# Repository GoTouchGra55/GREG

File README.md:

# GREG

GREG is a custom SBC designed to act as the main computer for a rover. It is built around the Allwinner T527 SoC and includes custom memory, power management, connectivity, camera, display, sensor, and motor-control hardware.

CAD REPO - [REPO](https://github.com/unknowngamer69/Orion-Rover)

## Hardware

- SoC: Allwinner T527
- RAM: 2 GB Samsung LPDDR4
- PMIC: AXP717-family
- Storage: MicroSD
- Networking: Ethernet
- Connectivity: 2× USB-A + 1× USB-C
- Display: HDMI + 5" LCD interface
- Cameras: 3-camera support (2 with multiplexing)
- Sensors: 6× ToF + LiDAR
- Debug: UART/debug connector
- Expansion: External breakout connector

## Motor Driver

Motor control is handled by a separate PCB instead of the T527.

- MCU: STM32G4
- Motor drivers: 3× DRV8262
- Motors: 6× brushed DC motors with built-in encoders

Separating the motor controller from the SBC keeps the main PCB free from clutter and noise.

## Schematics

SBC - [SEE SCHEMATICS](<Schematics(PDF)/GREG.pdf>)  
Motor Driver - [SEE SCHEMATICS](<Schematics(PDF)/GREG-MTRDRV.pdf>)

## Routing

### Motor Driver

### SBC (incomplete)

## Authors

Shaurya (Electronics) - [@GoTouchGra55](https://github.com/GoTouchGra55)  
Krish (CAD) - [@unknowngamer69](https://github.com/unknowngamer69)

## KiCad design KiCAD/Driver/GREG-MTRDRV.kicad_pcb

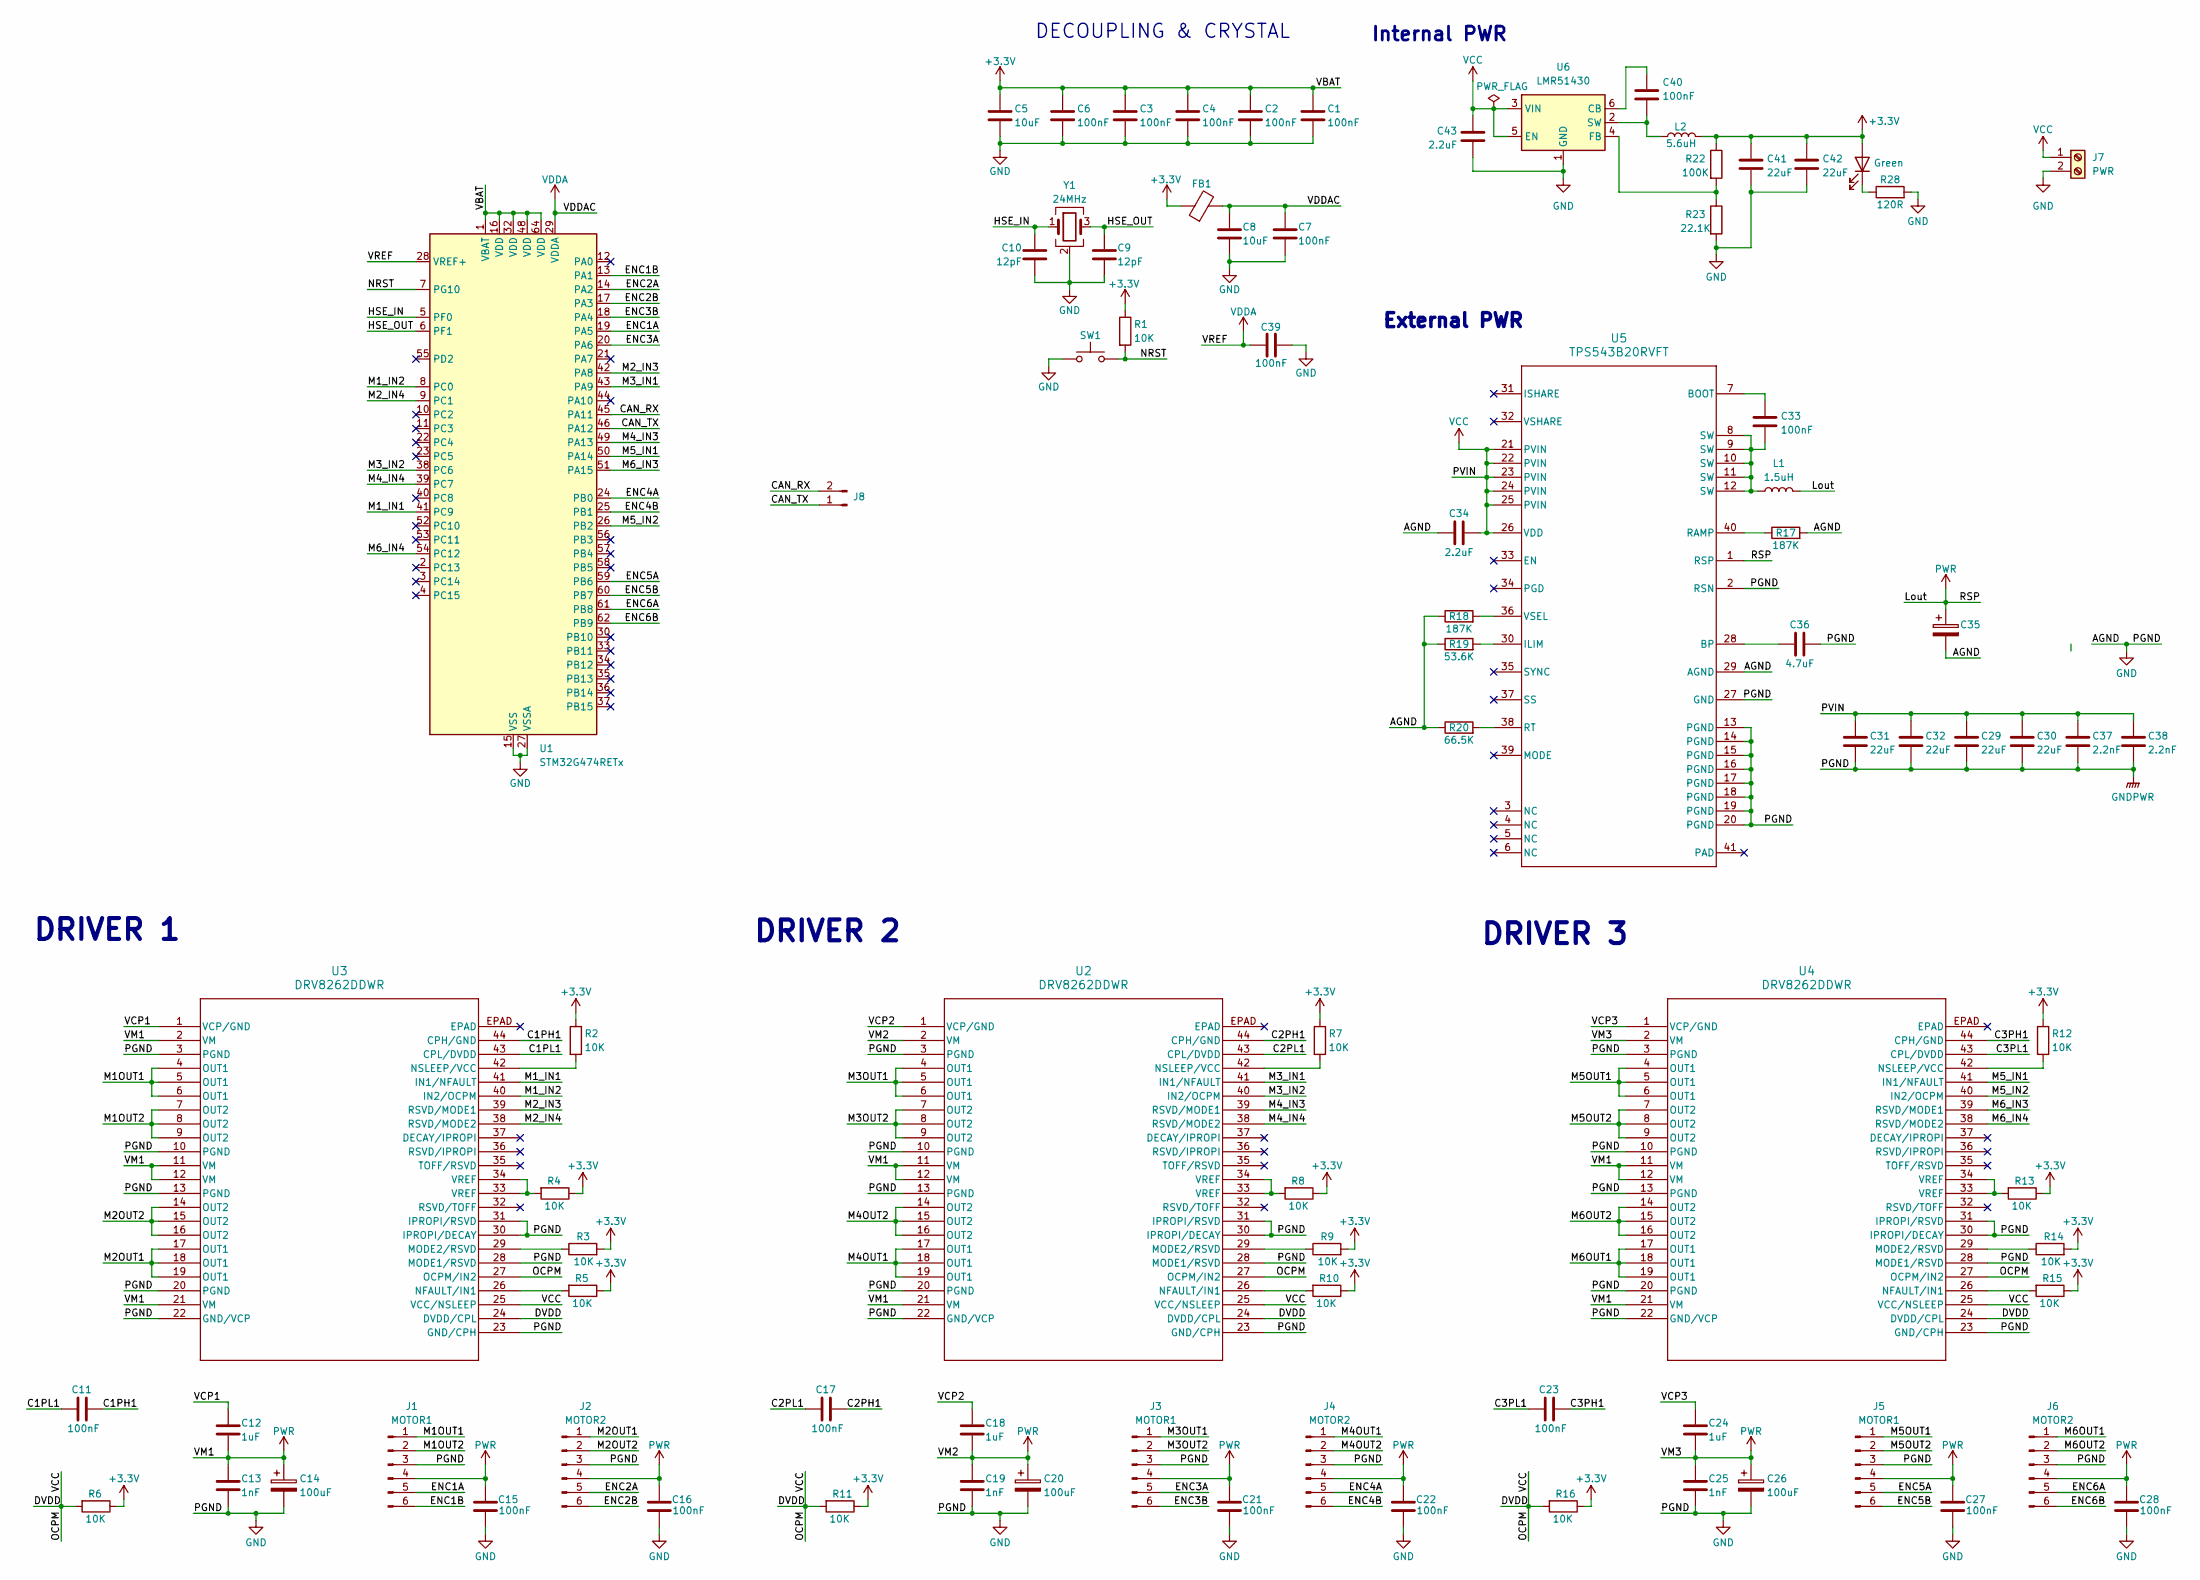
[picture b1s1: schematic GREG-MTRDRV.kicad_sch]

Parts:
C1, C2, C3, C4, C6, C7, C11, C15, C16, C17, C21, C22, C23, C27, C28, C33, C39, C40: 100nF; C_0402_1005Metric
C5, C8: 10uF; C_0603_1608Metric
C9, C10: 12pF; C_0402_1005Metric
C12, C18, C24: 1uF; C_0603_1608Metric
C13, C19, C25: 1nF; C_0402_1005Metric
C14, C20, C26: 100uF; C_Elec_6.3x7.7
C29, C30, C31, C32, C41, C42: 22uF; C_0603_1608Metric
C34, C43: 2.2uF; C_0603_1608Metric
C35: 1000uF; C_Elec_10x10.2
C36: 4.7uF; C_0603_1608Metric
C37, C38: 2.2nF; C_0603_1608Metric
FB1: FerriteBead; D_0603_1608Metric
Int_Indicator1: Green; LED_0402_1005Metric
J1, J3, J5: MOTOR1; JST_EH_B6B-EH-A_1x06_P2.50mm_Vertical
J2, J4, J6: MOTOR2; JST_EH_B6B-EH-A_1x06_P2.50mm_Vertical
J7: PWR; TerminalBlock_Phoenix_MKDS-1,5-2-5.08_1x02_P5.08mm_Horizont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
J8: Conn_01x02_Pin; JST_XH_B2B-XH-AM_1x02_P2.50mm_Vertical
L1: 1.5uH; L_Cenker_CKCS4018
L2: 5.6uH; L_Cenker_CKCS252010
R1, R2, R3, R4, R5, R6, R7, R8, R9, R10, R11, R12, R13, R14, R15, R16: 10K; R_0603_1608Metric
R17, R18: 187K; R_0603_1608Metric
R19: 53.6K; R_0603_1608Metric
R20: 66.5K; R_0603_1608Metric
R22: 100K; R_0603_1608Metric
R23: 22.1K; R_0603_1608Metric
R28: 120R; R_0603_1608Metric
SW1: SW_Push; SW_Push_SPST_NO_Alps_SKRK
U1: STM32G474RETx; LQFP-64_10x10mm_P0.5mm
U2, U3, U4: DRV8262DDWR; HTSSOP44-DDW_TEX
U5: TPS543B20RVFT; RVF0040A
U6: LMR51430; SOT-23-6
Y1: 24MHz; Crystal_SMD_3225-4Pin_3.2x2.5mm

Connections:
+3.3V: C1.1, C2.1, C3.1, C4.1, C5.1, C6.1, C41.1, C42.1, FB1.1, Int_Indicator1.2 (A), L2.1, R1.1, R2.1, R3.2, R4.1, R5.1, R6.1, R7.1, R8.1, R9.2, R10.1, R11.1, R12.1, R13.1, R14.2, R15.1, R16.1, R22.1, U1.1 (VBAT), U1.16 (VDD), U1.32 (VDD), U1.48 (VDD), U1.64 (VDD)
/C1PH1: C11.2, U3.44 (CPH/GND)
/C1PL1: C11.1, U3.43 (CPL/DVDD)
/C2PH1: C17.2, U2.44 (CPH/GND)
/C2PL1: C17.1, U2.43 (CPL/DVDD)
/C3PH1: C23.2, U4.44 (CPH/GND)
/C3PL1: C23.1, U4.43 (CPL/DVDD)
/CAN_RX: J8.2, U1.45 (PA11)
/CAN_TX: J8.1, U1.46 (PA12)
/ENC1A: J1.5, U1.19 (PA5)
/ENC1B: J1.6, U1.13 (PA1)
/ENC2A: J2.5, U1.14 (PA2)
/ENC2B: J2.6, U1.17 (PA3)
/ENC3A: J3.5, U1.20 (PA6)
/ENC3B: J3.6, U1.18 (PA4)
/ENC4A: J4.5, U1.24 (PB0)
/ENC4B: J4.6, U1.25 (PB1)
/ENC5A: J5.5, U1.59 (PB6)
/ENC5B: J5.6, U1.60 (PB7)
/ENC6A: J6.5, U1.61 (PB8)
/ENC6B: J6.6, U1.62 (PB9)
/HSE_IN: C10.1, U1.5 (PF0), Y1.1
/HSE_OUT: C9.1, U1.6 (PF1), Y1.3
/M1OUT1: J1.1, U3.4 (OUT1), U3.5 (OUT1), U3.6 (OUT1)
/M1OUT2: J1.2, U3.7 (OUT2), U3.8 (OUT2), U3.9 (OUT2)
/M1_IN1: U1.41 (PC9), U3.41 (IN1/NFAULT)
/M1_IN2: U1.8 (PC0), U3.40 (IN2/OCPM)
/M2OUT1: J2.1, U3.17 (OUT1), U3.18 (OUT1), U3.19 (OUT1)
/M2OUT2: J2.2, U3.14 (OUT2), U3.15 (OUT2), U3.16 (OUT2)
/M2_IN3: U1.42 (PA8), U3.39 (RSVD/MODE1)
/M2_IN4: U1.9 (PC1), U3.38 (RSVD/MODE2)
/M3OUT1: J3.1, U2.4 (OUT1), U2.5 (OUT1), U2.6 (OUT1)
/M3OUT2: J3.2, U2.7 (OUT2), U2.8 (OUT2), U2.9 (OUT2)
/M3_IN1: U1.43 (PA9), U2.41 (IN1/NFAULT)
/M3_IN2: U1.38 (PC6), U2.40 (IN2/OCPM)
/M4OUT1: J4.1, U2.17 (OUT1), U2.18 (OUT1), U2.19 (OUT1)
/M4OUT2: J4.2, U2.14 (OUT2), U2.15 (OUT2), U2.16 (OUT2)
/M4_IN3: U1.49 (PA13), U2.39 (RSVD/MODE1)
/M4_IN4: U1.39 (PC7), U2.38 (RSVD/MODE2)
/M5OUT1: J5.1, U4.4 (OUT1), U4.5 (OUT1), U4.6 (OUT1)
/M5OUT2: J5.2, U4.7 (OUT2), U4.8 (OUT2), U4.9 (OUT2)
/M5_IN1: U1.50 (PA14), U4.41 (IN1/NFAULT)
/M5_IN2: U1.26 (PB2), U4.40 (IN2/OCPM)
/M6OUT1: J6.1, U4.17 (OUT1), U4.18 (OUT1), U4.19 (OUT1)
/M6OUT2: J6.2, U4.14 (OUT2), U4.15 (OUT2), U4.16 (OUT2)
/M6_IN3: U1.51 (PA15), U4.39 (RSVD/MODE1)
/M6_IN4: U1.54 (PC12), U4.38 (RSVD/MODE2)
/NRST: R1.2, SW1.2, U1.7 (PG10)
/VCP1: C12.1, U3.1 (VCP/GND)
/VCP2: C18.1, U2.1 (VCP/GND)
/VCP3: C24.1, U4.1 (VCP/GND)
GND: C1.2, C2.2, C3.2, C4.2, C5.2, C6.2, C7.2, C8.2, C9.2, C10.2, C13.2, C14.2, C15.2, C16.2, C19.2, C20.2, C21.2, C22.2, C25.2, C26.2, C27.2, C28.2, C29.2, C30.2, C31.2, C32.2, C34.1, C35.2, C36.2, C37.2, C38.2, C39.1, C41.2, C42.2, C43.2, J1.3, J2.3, J3.3, J4.3, J5.3, J6.3, J7.2, R17.2, R18.1, R19.1, R20.1, R23.2, R28.2, SW1.1, U1.15 (VSS), U1.27 (VSSA), U1.31 (VSS), U1.47 (VSS), U1.63 (VSS), U2.3 (PGND), U2.10 (PGND), U2.13 (PGND), U2.20 (PGND), U2.22 (GND/VCP), U2.23 (GND/CPH), U2.28 (MODE1/RSVD), U2.30 (IPROPI/DECAY), U2.31 (IPROPI/RSVD), U3.3 (PGND), U3.10 (PGND), U3.13 (PGND), U3.20 (PGND), U3.22 (GND/VCP), U3.23 (GND/CPH), U3.28 (MODE1/RSVD), U3.30 (IPROPI/DECAY), U3.31 (IPROPI/RSVD), U4.3 (PGND), U4.10 (PGND), U4.13 (PGND), U4.20 (PGND), U4.22 (GND/VCP), U4.23 (GND/CPH), U4.28 (MODE1/RSVD), U4.30 (IPROPI/DECAY), U4.31 (IPROPI/RSVD), U5.2 (RSN), U5.13 (PGND), U5.14 (PGND), U5.15 (PGND), U5.16 (PGND), U5.17 (PGND), U5.18 (PGND), U5.19 (PGND), U5.20 (PGND), U5.27 (GND), U5.29 (AGND), U6.1 (GND), Y1.2 (G), Y1.4 (G)
unnamed: C33.2, L1.1, U5.8 (SW), U5.9 (SW), U5.10 (SW), U5.11 (SW), U5.12 (SW)
unnamed: Int_Indicator1.1 (K), R28.1
unnamed: R4.2, U3.33 (VREF), U3.34 (VREF)
unnamed: R8.2, U2.33 (VREF), U2.34 (VREF)
unnamed: R13.2, U4.33 (VREF), U4.34 (VREF)
unnamed: R9.1, U2.29 (MODE2/RSVD)
unnamed: R10.2, U2.26 (NFAULT/IN1)
unnamed: R7.2, U2.42 (NSLEEP/VCC)
unnamed: R3.1, U3.29 (MODE2/RSVD)
unnamed: R5.2, U3.26 (NFAULT/IN1)
unnamed: R2.2, U3.42 (NSLEEP/VCC)
unnamed: R14.1, U4.29 (MODE2/RSVD)
unnamed: R15.2, U4.26 (NFAULT/IN1)
unnamed: R12.2, U4.42 (NSLEEP/VCC)
unnamed: C33.1, U5.7 (BOOT)
unnamed: C36.1, U5.28 (BP)
unnamed: R19.2, U5.30 (ILIM)
unnamed: R17.1, U5.40 (RAMP)
unnamed: R20.2, U5.38 (RT)
unnamed: R18.2, U5.36 (VSEL)
unnamed: C40.1, U6.6 (CB)
unnamed: R22.2, R23.1, U6.4 (FB)
unnamed: C40.2, L2.2, U6.2 (SW)
VDDA: C7.1, C8.1, C39.2, FB1.2, U1.28 (VREF+), U1.29 (VDDA)

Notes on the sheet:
DECOUPLING & CRYSTAL
DRIVER 3
DRIVER 1
DRIVER 2
External PWR
Internal PWR

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
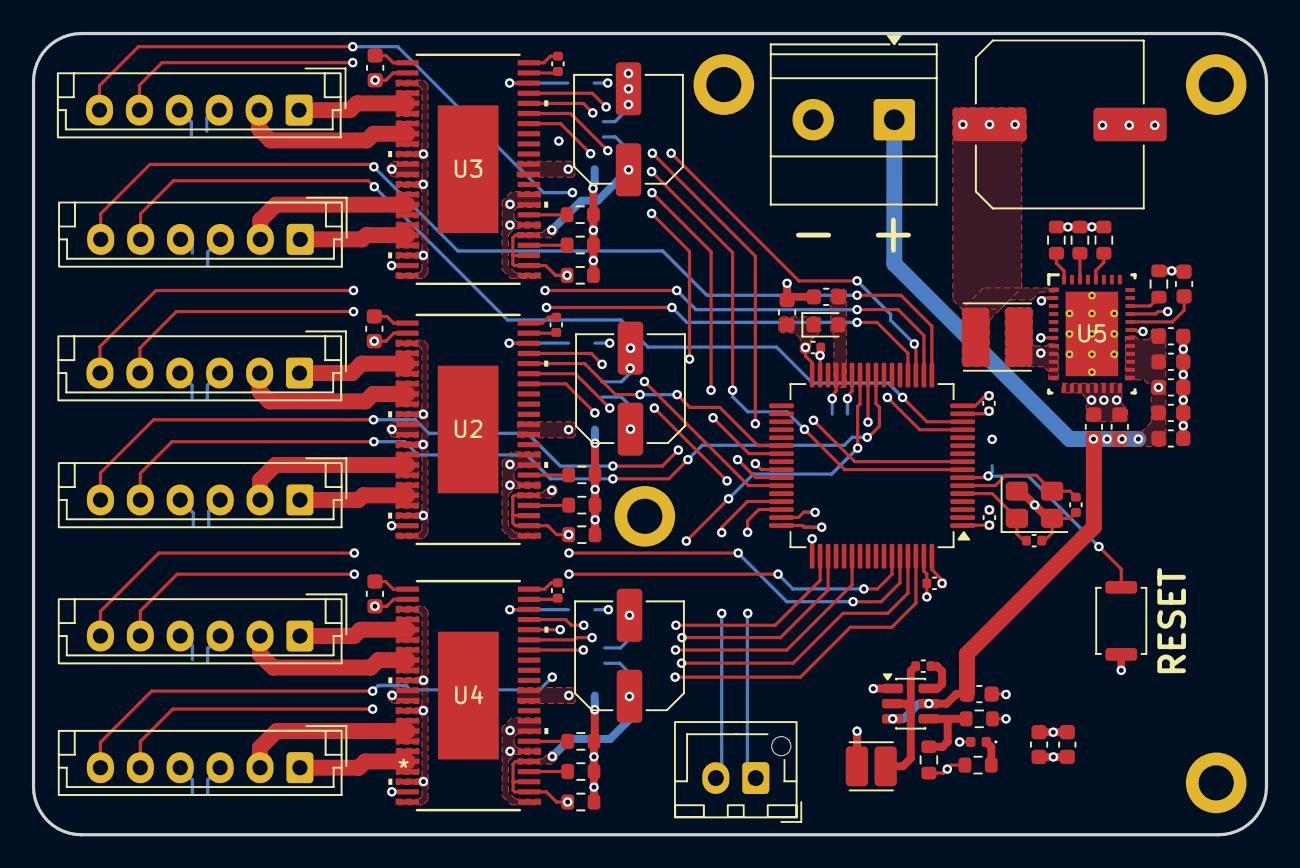
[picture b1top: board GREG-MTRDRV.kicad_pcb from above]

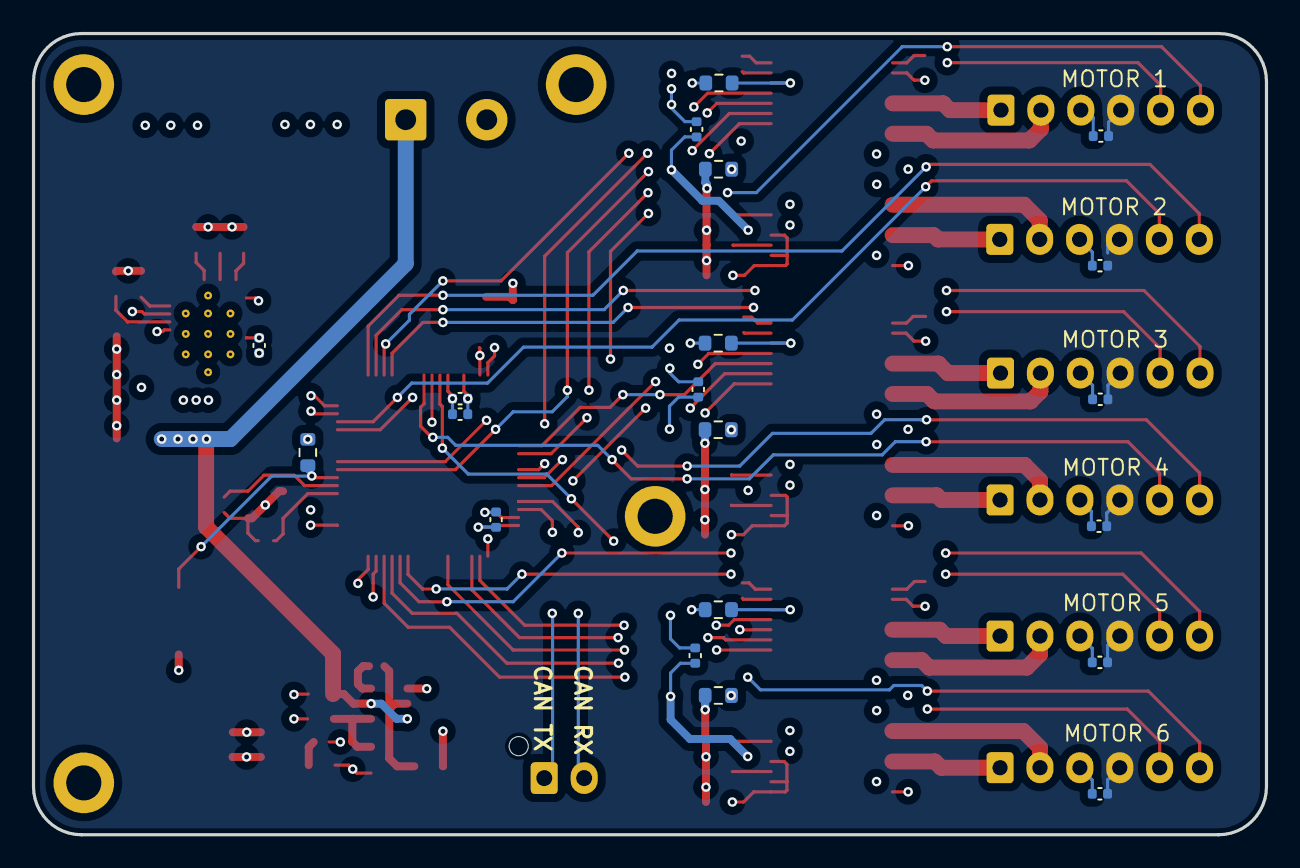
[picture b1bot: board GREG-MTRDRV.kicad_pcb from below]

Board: 4 copper layers, 77.2 x 50.2 mm, 86 parts (20 on the bottom side), 79 nets.

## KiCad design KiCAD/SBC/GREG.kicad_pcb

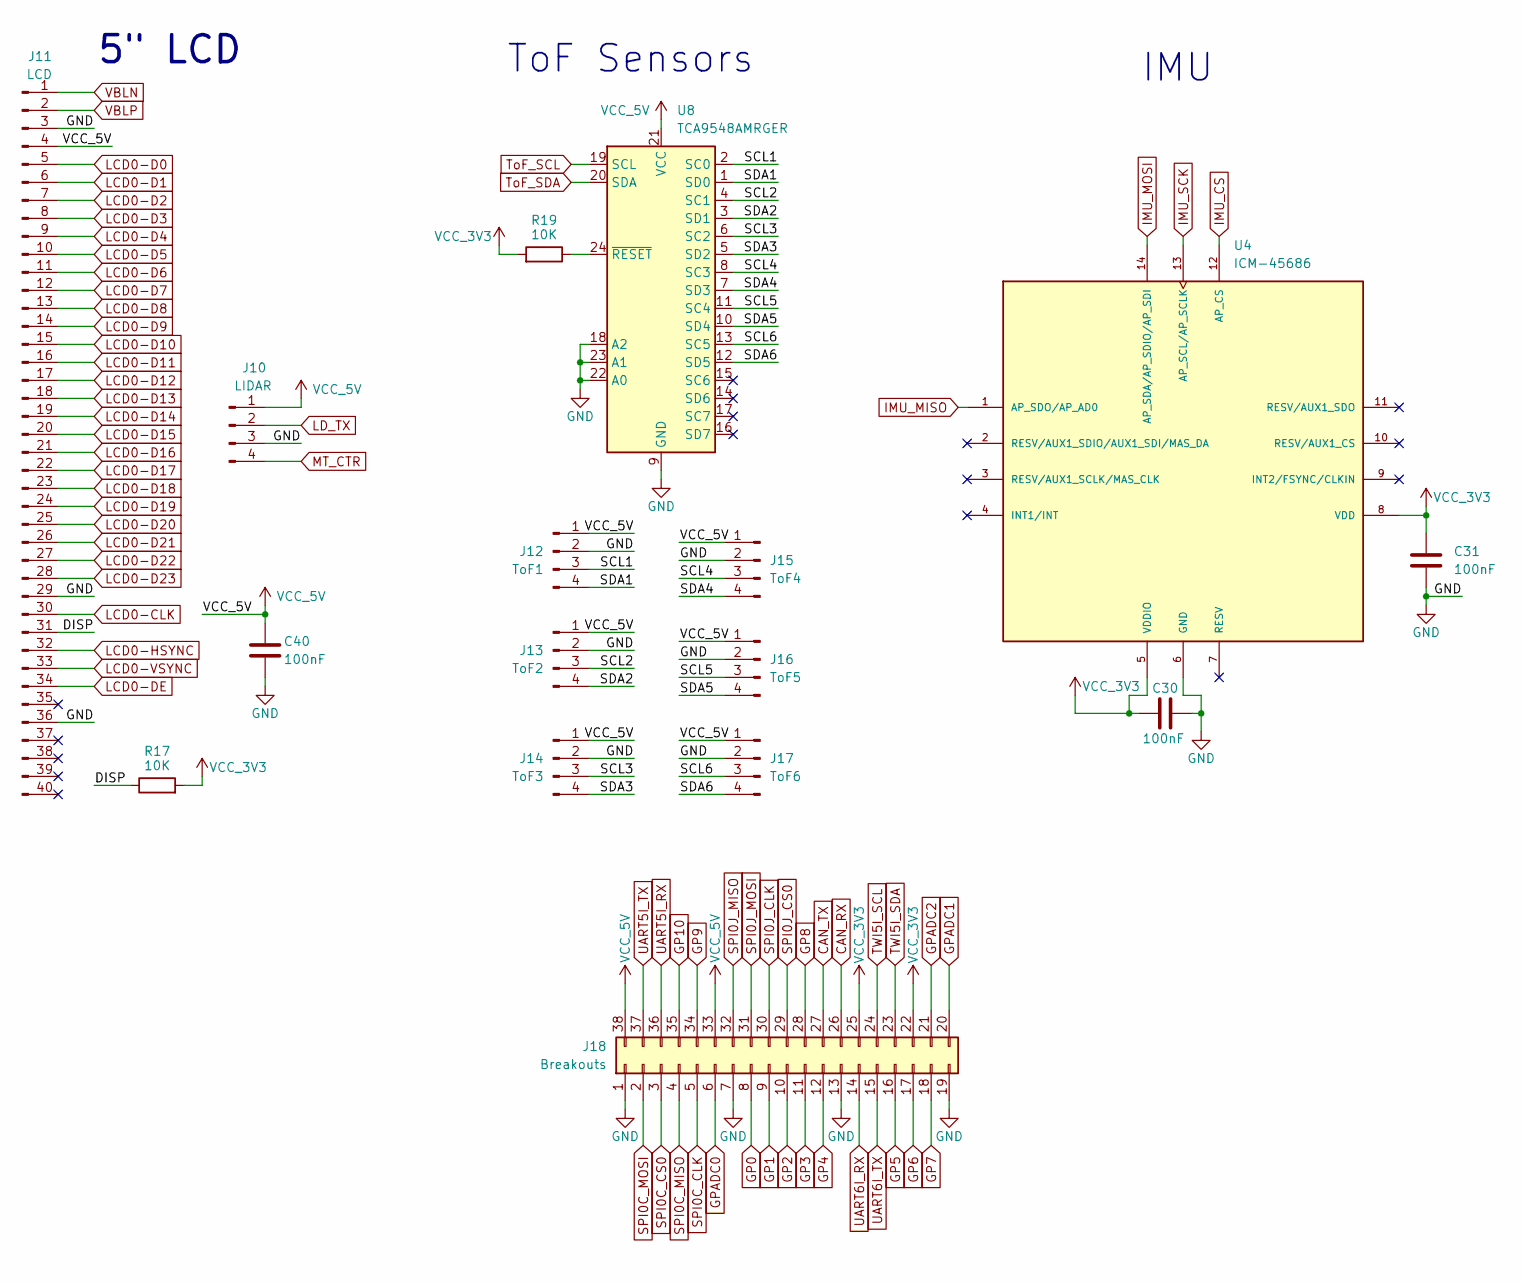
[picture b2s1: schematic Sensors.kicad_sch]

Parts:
C30, C31, C40: 100nF; C_0402_1005Metric
J10: LIDAR; JST_EH_B4B-EH-A_1x04_P2.50mm_Vertical
J11: LCD; TE_4-1734839-0_1x40-1MP_P0.5mm_Horizontal
J12: ToF1; JST_EH_B4B-EH-A_1x04_P2.50mm_Vertical
J13: ToF2; JST_EH_B4B-EH-A_1x04_P2.50mm_Vertical
J14: ToF3; JST_EH_B4B-EH-A_1x04_P2.50mm_Vertical
J15: ToF4; JST_EH_B4B-EH-A_1x04_P2.50mm_Vertical
J16: ToF5; JST_EH_B4B-EH-A_1x04_P2.50mm_Vertical
J17: ToF6; JST_EH_B4B-EH-A_1x04_P2.50mm_Vertical
J18: Breakouts; PinHeader_2x19_P2.54mm_Vertical
R17, R19: 10K; R_0402_1005Metric
U4: ICM-45686; IC_ICM-45686
U8: TCA9548AMRGER; Texas_RGE0024C_VQFN-24-1EP_4x4mm_P0.5mm_EP2.1x2.1mm

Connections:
/Sensors/DISP: J11.31, R17.1
/Sensors/SCL1: J12.3, U8.2 (SC0)
/Sensors/SCL2: J13.3, U8.4 (SC1)
/Sensors/SCL3: J14.3, U8.6 (SC2)
/Sensors/SCL4: J15.3, U8.8 (SC3)
/Sensors/SCL5: J16.3, U8.11 (SC4)
/Sensors/SCL6: J17.3, U8.13 (SC5)
/Sensors/SDA1: J12.4, U8.1 (SD0)
/Sensors/SDA2: J13.4, U8.3 (SD1)
/Sensors/SDA3: J14.4, U8.5 (SD2)
/Sensors/SDA4: J15.4, U8.7 (SD3)
/Sensors/SDA5: J16.4, U8.10 (SD4)
/Sensors/SDA6: J17.4, U8.12 (SD5)
CAN_RX: J18.26; also elsewhere on the board
CAN_TX: J18.27; also elsewhere on the board
GND: C30.2, C31.2, C40.2, J10.3, J11.3, J11.29, J11.36, J12.2, J13.2, J14.2, J15.2, J16.2, J17.2, J18.1, J18.7, J18.13, J18.19, U4.6 (GND), U8.9 (GND), U8.18 (A2), U8.22 (A0), U8.23 (A1); also elsewhere on the board
GP0: J18.8; also elsewhere on the board
GP1: J18.9; also elsewhere on the board
GP2: J18.10; also elsewhere on the board
GP3: J18.11; also elsewhere on the board
GP4: J18.12; also elsewhere on the board
GP5: J18.16; also elsewhere on the board
GP6: J18.17; also elsewhere on the board
GP7: J18.18; also elsewhere on the board
GP8: J18.28; also elsewhere on the board
GP9: J18.34; also elsewhere on the board
GP10: J18.35; also elsewhere on the board
GPADC0: J18.6; also elsewhere on the board
GPADC1: J18.20; also elsewhere on the board
GPADC2: J18.21; also elsewhere on the board
IMU_CS: U4.12 (AP_CS); also elsewhere on the board
IMU_MISO: U4.1 (AP_SDO/AP_AD0); also elsewhere on the board
IMU_MOSI: U4.14 (AP_SDA/AP_SDIO/AP_SDI); also elsewhere on the board
IMU_SCK: U4.13 (AP_SCL/AP_SCLK); also elsewhere on the board
LCD0-CLK: J11.30; also elsewhere on the board
LCD0-D0: J11.5; also elsewhere on the board
LCD0-D1: J11.6; also elsewhere on the board
LCD0-D2: J11.7; also elsewhere on the board
LCD0-D3: J11.8; also elsewhere on the board
LCD0-D4: J11.9; also elsewhere on the board
LCD0-D5: J11.10; also elsewhere on the board
LCD0-D6: J11.11; also elsewhere on the board
LCD0-D7: J11.12; also elsewhere on the board
LCD0-D8: J11.13; also elsewhere on the board
LCD0-D9: J11.14; also elsewhere on the board
LCD0-D10: J11.15; also elsewhere on the board
LCD0-D11: J11.16; also elsewhere on the board
LCD0-D12: J11.17; also elsewhere on the board
LCD0-D13: J11.18; also elsewhere on the board
LCD0-D14: J11.19; also elsewhere on the board
LCD0-D15: J11.20; also elsewhere on the board
LCD0-D16: J11.21; also elsewhere on the board
LCD0-D17: J11.22; also elsewhere on the board
LCD0-D18: J11.23; also elsewhere on the board
LCD0-D19: J11.24; also elsewhere on the board
LCD0-D20: J11.25; also elsewhere on the board
LCD0-D21: J11.26; also elsewhere on the board
LCD0-D22: J11.27; also elsewhere on the board
LCD0-D23: J11.28; also elsewhere on the board
LCD0-DE: J11.34; also elsewhere on the board
LCD0-HSYNC: J11.32; also elsewhere on the board
LCD0-VSYNC: J11.33; also elsewhere on the board
LD_TX: J10.2; also elsewhere on the board
MT_CTR: J10.4; also elsewhere on the board
unnamed: R19.1, U8.24 (~RESET)
SPI0C_CLK: J18.5; also elsewhere on the board
SPI0C_CS0: J18.3; also elsewhere on the board
SPI0C_MISO: J18.4; also elsewhere on the board
SPI0C_MOSI: J18.2; also elsewhere on the board
SPI0J_CLK: J18.30; also elsewhere on the board
SPI0J_CS0: J18.29; also elsewhere on the board
SPI0J_MISO: J18.32; also elsewhere on the board
SPI0J_MOSI: J18.31; also elsewhere on the board
TWI5I_SCL: J18.24; also elsewhere on the board
TWI5I_SDA: J18.23; also elsewhere on the board
ToF_SCL: U8.19 (SCL); also elsewhere on the board
ToF_SDA: U8.20 (SDA); also elsewhere on the board
UART5I_RX: J18.36; also elsewhere on the board
UART5I_TX: J18.37; also elsewhere on the board
UART6I_RX: J18.14; also elsewhere on the board
UART6I_TX: J18.15; also elsewhere on the board
VBLN: J11.1; also elsewhere on the board
VBLP: J11.2; also elsewhere on the board
VCC_3V3: C30.1, C31.1, J18.22, J18.25, R17.2, R19.2, U4.5 (VDDIO), U4.8 (VDD); also elsewhere on the board
VCC_5V: C40.1, J10.1, J11.4, J12.1, J13.1, J14.1, J15.1, J16.1, J17.1, J18.33, J18.38, U8.21 (VCC); also elsewhere on the board

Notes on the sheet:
5" LCD
ToF Sensors
IMU

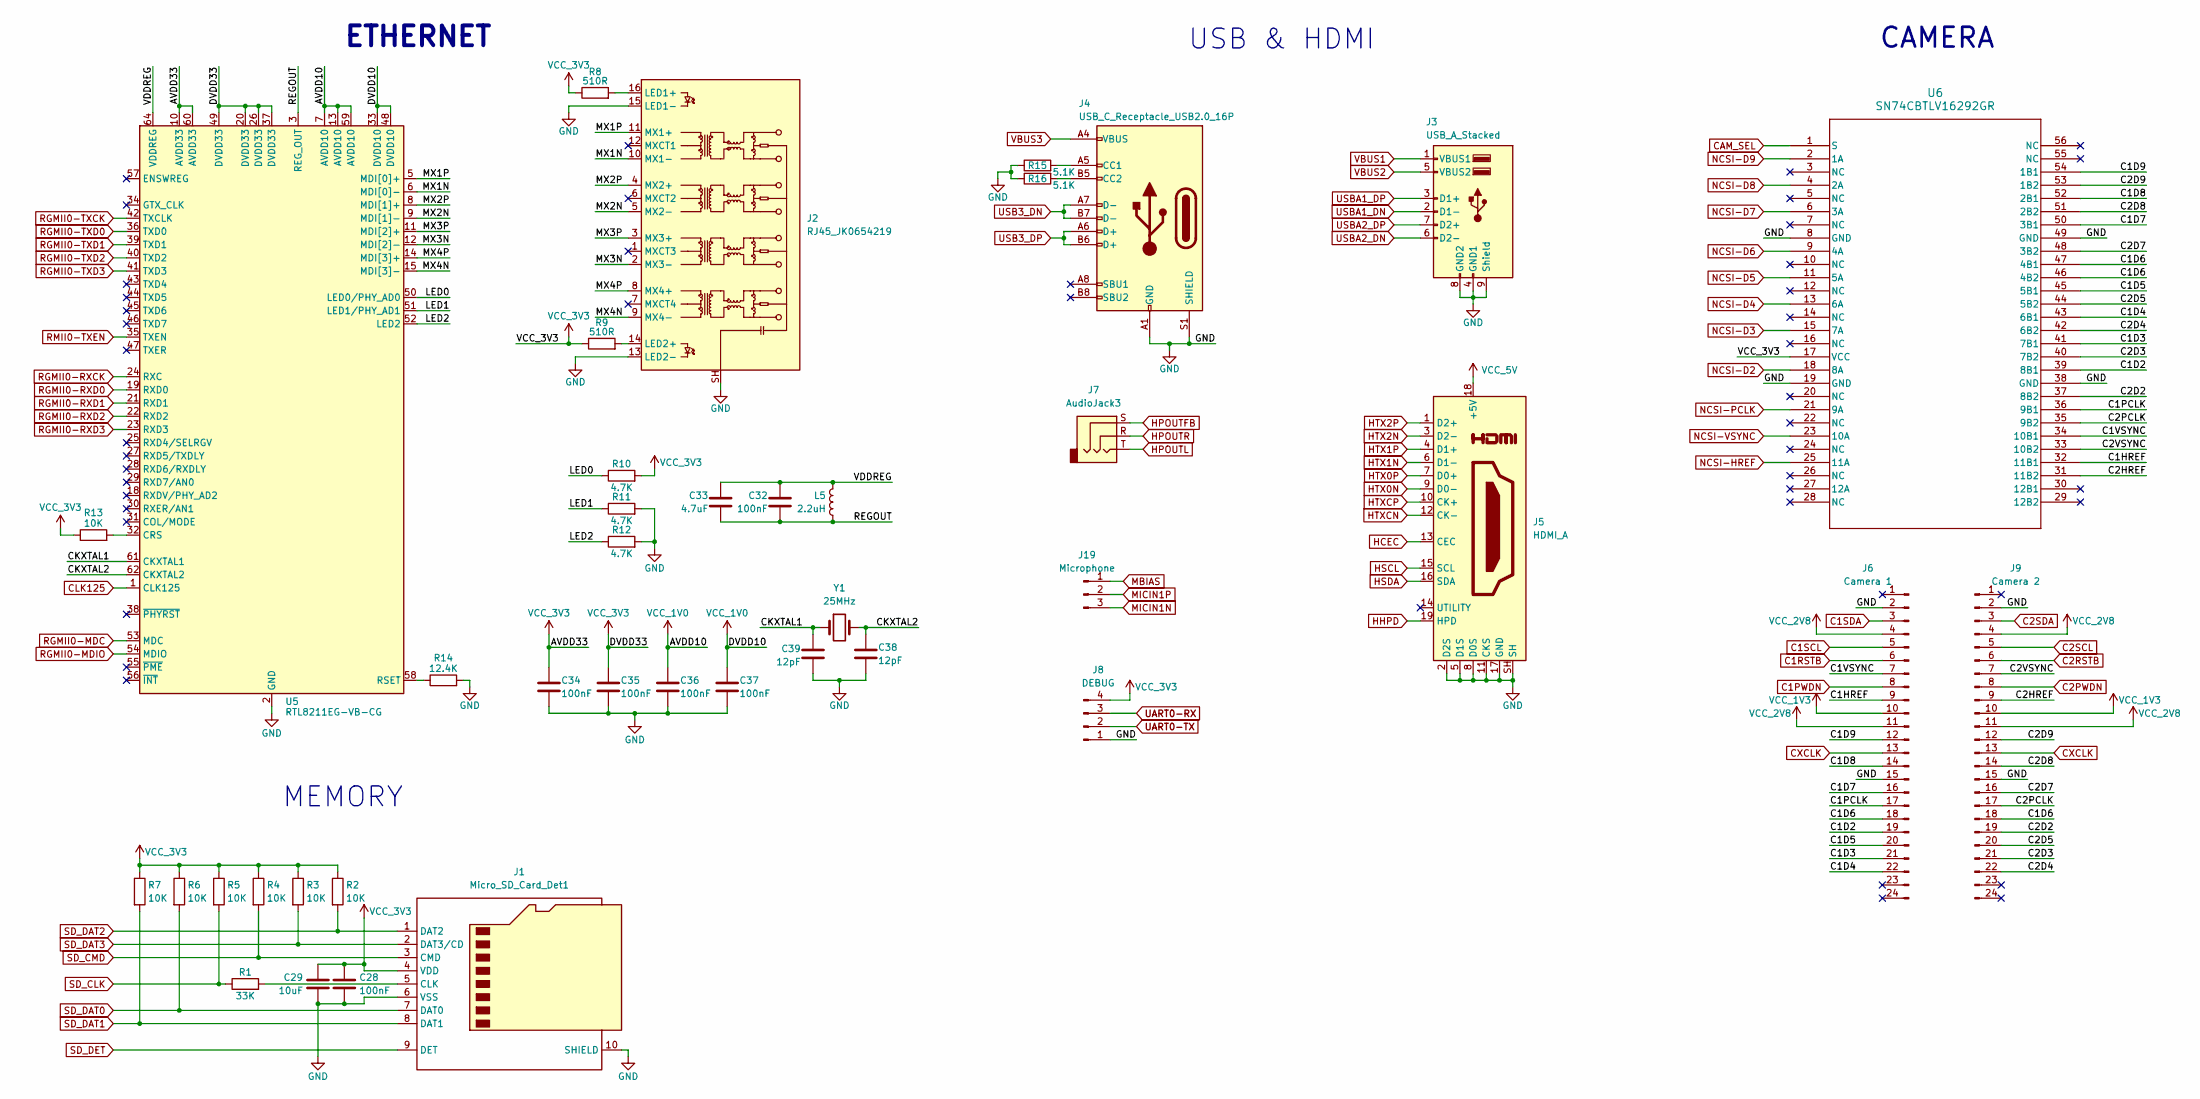
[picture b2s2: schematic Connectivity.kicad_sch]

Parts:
C28, C32, C34, C35, C36, C37: 100nF; C_0402_1005Metric
C29: 10uF; C_0805_2012Metric
C33: 4.7uF; C_0805_2012Metric
C38, C39: 12pF; C_0402_1005Metric
J1: Micro_SD_Card_Det1; microSD_HC_Wuerth
J2: RJ45_JK0654219; RJ45_Pulse_JK0654219NL_Horizontal
J3: USB_A_Stacked; USB_A_CUI_UJ2-ADH-TH_Horizontal_Stacked
J4: USB_C_Receptacle_USB2.0_16P; USB_C_Receptacle_HRO_TYPE-C-31-M-12
J5: HDMI_A; HDMI_Micro-D_Molex_46765-1xxx
J6: Camera 1; Molex_502231-2400_1x24-1SH_P0.5mm_Vertical
J7: AudioJack3; Jack_3.5mm_CUI_SJ-3523-SMT_Horizontal
J8: DEBUG; JST_EH_B4B-EH-A_1x04_P2.50mm_Vertical
J9: Camera 2; Molex_502231-2400_1x24-1SH_P0.5mm_Vertical
J19: Microphone; JST_EH_B3B-EH-A_1x03_P2.50mm_Vertical
L5: 2.2uH; L_Cenker_CKCS3015
R1: 33K; R_0402_1005Metric
R2, R3, R4, R5, R6, R7, R13: 10K; R_0402_1005Metric
R8, R9: 510R; R_0402_1005Metric
R10, R11, R12: 4.7K; R_0402_1005Metric
R14: 12.4K; R_0402_1005Metric
R15, R16: 5.1K; R_0402_1005Metric
U5: RTL8211EG-VB-CG; RTL
U6: SN74CBTLV16292GR; DGG56
Y1: 25MHz; Crystal_SMD_3215-2Pin_3.2x1.5mm

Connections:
/Connectivity/C1D2: J6.19, U6.39 (8B1)
/Connectivity/C1D3: J6.21, U6.41 (7B1)
/Connectivity/C1D4: J6.22, U6.43 (6B1)
/Connectivity/C1D5: J6.20, U6.45 (5B1)
/Connectivity/C1D6: J6.18, J9.18, U6.46 (4B2), U6.47 (4B1)
/Connectivity/C1D7: J6.16, U6.50 (3B1)
/Connectivity/C1D8: J6.14, U6.52 (2B1)
/Connectivity/C1D9: J6.12, U6.54 (1B1)
/Connectivity/C1HREF: J6.9, U6.32 (11B1)
/Connectivity/C1PCLK: J6.17, U6.36 (9B1)
/Connectivity/C1VSYNC: J6.7, U6.34 (10B1)
/Connectivity/C2D2: J9.19, U6.37 (8B2)
/Connectivity/C2D3: J9.21, U6.40 (7B2)
/Connectivity/C2D4: J9.22, U6.42 (6B2)
/Connectivity/C2D5: J9.20, U6.44 (5B2)
/Connectivity/C2D7: J9.16, U6.48 (3B2)
/Connectivity/C2D8: J9.14, U6.51 (2B2)
/Connectivity/C2D9: J9.12, U6.53 (1B2)
/Connectivity/C2HREF: J9.9, U6.31 (11B2)
/Connectivity/C2PCLK: J9.17, U6.35 (9B2)
/Connectivity/C2VSYNC: J9.7, U6.33 (10B2)
/Connectivity/CKXTAL1: C39.1, U5.61 (CKXTAL1), Y1.1
/Connectivity/CKXTAL2: C38.1, U5.62 (CKXTAL2), Y1.2
/Connectivity/LED0: R10.1, U5.50 (LED0/PHY_AD0)
/Connectivity/LED1: R11.1, U5.51 (LED1/PHY_AD1)
/Connectivity/LED2: R12.1, U5.52 (LED2)
/Connectivity/MX1N: J2.10 (MX1-), U5.6 (MDI[0]-)
/Connectivity/MX1P: J2.11 (MX1+), U5.5 (MDI[0]+)
/Connectivity/MX2N: J2.5 (MX2-), U5.9 (MDI[1]-)
/Connectivity/MX2P: J2.4 (MX2+), U5.8 (MDI[1]+)
/Connectivity/MX3N: J2.2 (MX3-), U5.12 (MDI[2]-)
/Connectivity/MX3P: J2.3 (MX3+), U5.11 (MDI[2]+)
/Connectivity/MX4N: J2.9 (MX4-), U5.15 (MDI[3]-)
/Connectivity/MX4P: J2.8 (MX4+), U5.14 (MDI[3]+)
/Connectivity/REGOUT: C32.2, C33.2, L5.2, U5.3 (REG_OUT)
/Connectivity/VDDREG: C32.1, C33.1, L5.1, U5.64 (VDDREG)
C1PWDN: J6.8; also elsewhere on the board
C1RSTB: J6.6; also elsewhere on the board
C1SCL: J6.5; also elsewhere on the board
C1SDA: J6.3; also elsewhere on the board
C2PWDN: J9.8; also elsewhere on the board
C2RSTB: J9.6; also elsewhere on the board
C2SCL: J9.5; also elsewhere on the board
C2SDA: J9.3; also elsewhere on the board
CAM_SEL: U6.1 (S); also elsewhere on the board
CLK125: U5.1 (CLK125); also elsewhere on the board
CXCLK: J6.13, J9.13; also elsewhere on the board
GND: C28.2, C29.2, C34.2, C35.2, C36.2, C37.2, C38.2, C39.2, J1.6 (VSS), J1.10 (SHIELD), J2.13 (LED2-), J2.15 (LED1-), J2.SH, J3.4 (GND1), J3.8 (GND2), J3.9 (Shield), J4.A1 (GND), J4.A12 (GND), J4.B1 (GND), J4.B12 (GND), J4.S1 (SHIELD), J5.2 (D2S), J5.5 (D1S), J5.8 (D0S), J5.11 (CKS), J5.17 (GND), J5.SH, J6.2, J6.15, J8.1, J9.2, J9.15, R11.2, R12.2, R14.2, R15.1, R16.1, U5.2 (GND), U5.4 (GND), U5.63 (GND), U5.65 (GND), U6.8 (GND), U6.19 (GND), U6.38 (GND), U6.49 (GND); also elsewhere on the board
HCEC: J5.13 (CEC); also elsewhere on the board
HHPD: J5.19 (HPD); also elsewhere on the board
HPOUTFB: J7.S; also elsewhere on the board
HPOUTL: J7.T; also elsewhere on the board
HPOUTR: J7.R; also elsewhere on the board
HSCL: J5.15 (SCL); also elsewhere on the board
HSDA: J5.16 (SDA); also elsewhere on the board
HTX0N: J5.9 (D0-); also elsewhere on the board
HTX0P: J5.7 (D0+); also elsewhere on the board
HTX1N: J5.6 (D1-); also elsewhere on the board
HTX1P: J5.4 (D1+); also elsewhere on the board
HTX2N: J5.3 (D2-); also elsewhere on the board
HTX2P: J5.1 (D2+); also elsewhere on the board
HTXCN: J5.12 (CK-); also elsewhere on the board
HTXCP: J5.10 (CK+); also elsewhere on the board
MBIAS: J19.1; also elsewhere on the board
MICIN1N: J19.3; also elsewhere on the board
MICIN1P: J19.2; also elsewhere on the board
NCSI-D2: U6.18 (8A); also elsewhere on the board
NCSI-D3: U6.15 (7A); also elsewhere on the board
NCSI-D4: U6.13 (6A); also elsewhere on the board
NCSI-D5: U6.11 (5A); also elsewhere on the board
NCSI-D6: U6.9 (4A); also elsewhere on the board
NCSI-D7: U6.6 (3A); also elsewhere on the board
NCSI-D8: U6.4 (2A); also elsewhere on the board
NCSI-D9: U6.2 (1A); also elsewhere on the board
NCSI-HREF: U6.25 (11A); also elsewhere on the board
NCSI-PCLK: U6.21 (9A); also elsewhere on the board
NCSI-VSYNC: U6.23 (10A); also elsewhere on the board
unnamed: J1.5 (CLK), R1.2
unnamed: J2.16 (LED1+), R8.2
unnamed: J2.14 (LED2+), R9.2
unnamed: J4.A5 (CC1), R15.2
unnamed: J4.B5 (CC2), R16.2
unnamed: R13.2, U5.32 (CRS)
unnamed: R14.1, U5.58 (RSET)
RGMII0-MDC: U5.53 (MDC); also elsewhere on the board
RGMII0-MDIO: U5.54 (MDIO); also elsewhere on the board
RGMII0-RXCK: U5.24 (RXC); also elsewhere on the board
RGMII0-RXD0: U5.19 (RXD0); also elsewhere on the board
RGMII0-RXD1: U5.21 (RXD1); also elsewhere on the board
RGMII0-RXD2: U5.22 (RXD2); also elsewhere on the board
RGMII0-RXD3: U5.23 (RXD3); also elsewhere on the board
RGMII0-TXCK: U5.42 (TXCLK); also elsewhere on the board
RGMII0-TXD0: U5.36 (TXD0); also elsewhere on the board
RGMII0-TXD1: U5.39 (TXD1); also elsewhere on the board
RGMII0-TXD2: U5.40 (TXD2); also elsewhere on the board
RGMII0-TXD3: U5.41 (TXD3)
RMII0-TXEN: U5.35 (TXEN); also elsewhere on the board
SD_CLK: R1.1, R5.2
SD_CMD: J1.3 (CMD), R4.2
SD_DAT0: J1.7 (DAT0), R6.2
SD_DAT1: J1.8 (DAT1), R7.2
SD_DAT2: J1.1 (DAT2), R2.2
SD_DAT3: J1.2 (DAT3/CD), R3.2
SD_DET: J1.9 (DET)
UART0-RX: J8.3; also elsewhere on the board
UART0-TX: J8.2; also elsewhere on the board
USB3_DN: J4.A7 (D-), J4.B7 (D-); also elsewhere on the board
USB3_DP: J4.A6 (D+), J4.B6 (D+); also elsewhere on the board
USBA1_DN: J3.2 (D1-); also elsewhere on the board
USBA1_DP: J3.3 (D1+); also elsewhere on the board
USBA2_DN: J3.6 (D2-); also elsewhere on the board
USBA2_DP: J3.7 (D2+); also elsewhere on the board
VBUS1: J3.1 (VBUS1)
VBUS2: J3.5 (VBUS2)
VBUS3: J4.A4 (VBUS), J4.A9 (VBUS), J4.B4 (VBUS), J4.B9 (VBUS)
VCC_1V0: C36.1, C37.1, U5.7 (AVDD10), U5.13 (AVDD10), U5.33 (DVDD10), U5.48 (DVDD10), U5.59 (AVDD10); also elsewhere on the board
VCC_1V3: J6.10, J9.10; also elsewhere on the board
VCC_2V8: J6.4, J6.11, J9.4, J9.11; also elsewhere on the board
VCC_3V3: C28.1, C29.1, C34.1, C35.1, J1.4 (VDD), J8.4, R2.1, R3.1, R4.1, R5.1, R6.1, R7.1, R8.1, R9.1, R10.2, R13.1, U5.10 (AVDD33), U5.20 (DVDD33), U5.26 (DVDD33), U5.37 (DVDD33), U5.49 (DVDD33), U5.60 (AVDD33), U6.17 (VCC); also elsewhere on the board
VCC_5V: J5.18 (+5V); also elsewhere on the board

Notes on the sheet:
ETHERNET
CAMERA
USB & HDMI
MEMORY
